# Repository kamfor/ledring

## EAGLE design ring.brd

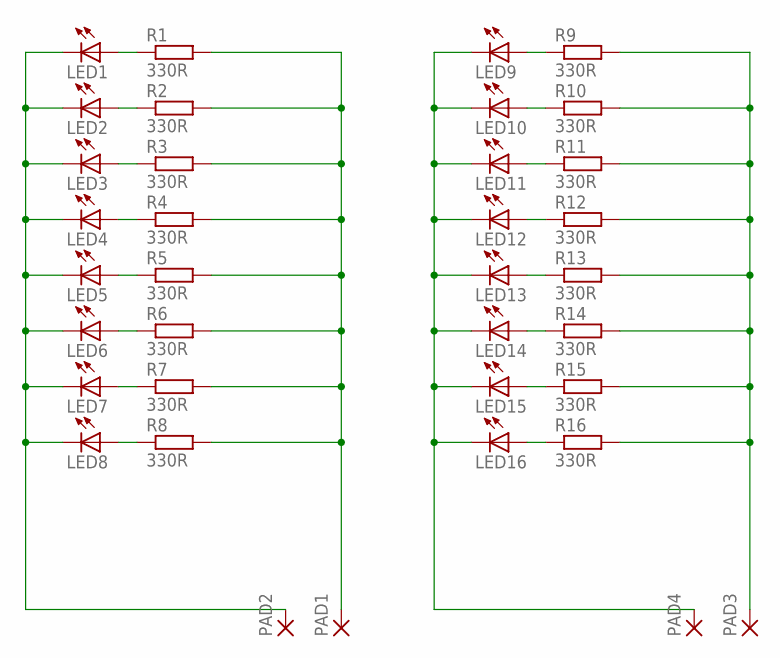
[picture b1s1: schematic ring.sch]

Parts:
LED1, LED2, LED3, LED4, LED5, LED6, LED7, LED8, LED9, LED10, LED11, LED12, LED13, LED14, LED15, LED16: LEDKA-3528ASYC; KA-3528ASYC
PAD1, PAD2, PAD3, PAD4: SMD2; SMD1,27-2,54
R1, R2, R3, R4, R5, R6, R7, R8, R9, R10, R11, R12, R13, R14, R15, R16: 330R; R0805W

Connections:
unnamed: PAD1.1, R1.2, R2.2, R3.2, R4.2, R5.2, R6.2, R7.2, R8.2
unnamed: LED1.C, LED2.C, LED3.C, LED4.C, LED5.C, LED6.C, LED7.C, LED8.C, PAD2.1
unnamed: LED1.A, R1.1
unnamed: LED2.A, R2.1
unnamed: LED3.A, R3.1
unnamed: LED4.A, R4.1
unnamed: LED5.A, R5.1
unnamed: LED6.A, R6.1
unnamed: LED7.A, R7.1
unnamed: LED8.A, R8.1
unnamed: PAD3.1, R9.2, R10.2, R11.2, R12.2, R13.2, R14.2, R15.2, R16.2
unnamed: LED9.C, LED10.C, LED11.C, LED12.C, LED13.C, LED14.C, LED15.C, LED16.C, PAD4.1
unnamed: LED9.A, R9.1
unnamed: LED10.A, R10.1
unnamed: LED11.A, R11.1
unnamed: LED12.A, R12.1
unnamed: LED13.A, R13.1
unnamed: LED14.A, R14.1
unnamed: LED15.A, R15.1
unnamed: LED16.A, R16.1

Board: 2 copper layers, 36 parts (0 on the bottom side), 20 nets, no tracks yet.

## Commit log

2016-05-27 initial
2016-06-11 placing
2016-06-24 dimensions
2016-06-24 skog
2016-07-02 angled
2016-07-26 curve
2016-09-09 polygon
2016-09-27 nentime
